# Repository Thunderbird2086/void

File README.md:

# VOID
## An Ergonomic 3x5 Split Keyboard

The VOID keyboard is meticulously designed to offer an ergonomic typing experience with its compact 3x5 layout. It supports a variety of switch types, including CherryMX, Choc V1/V2, and a hybrid configuration.

Similar to the [uniCorne](https://github.com/Thunderbird2086/uniCorne), the VOID keyboard features controller compatibility, hardware handedness, and Nice!View integration. Additionally, for communication between each side in wired keyboards using PR2040/ProMicro, it uses a USB Type-C connector instead of TRRS to avoid short circuit issues that can damage MCUs.

The pinky column is slightly splayed while the others are column staggered. For wireless keyboards, the VOID has a power connector to the MCU and an onboard pogo pin connector to the charger board, which can be directly connected to a battery.

## Images

## Build guide
TODO

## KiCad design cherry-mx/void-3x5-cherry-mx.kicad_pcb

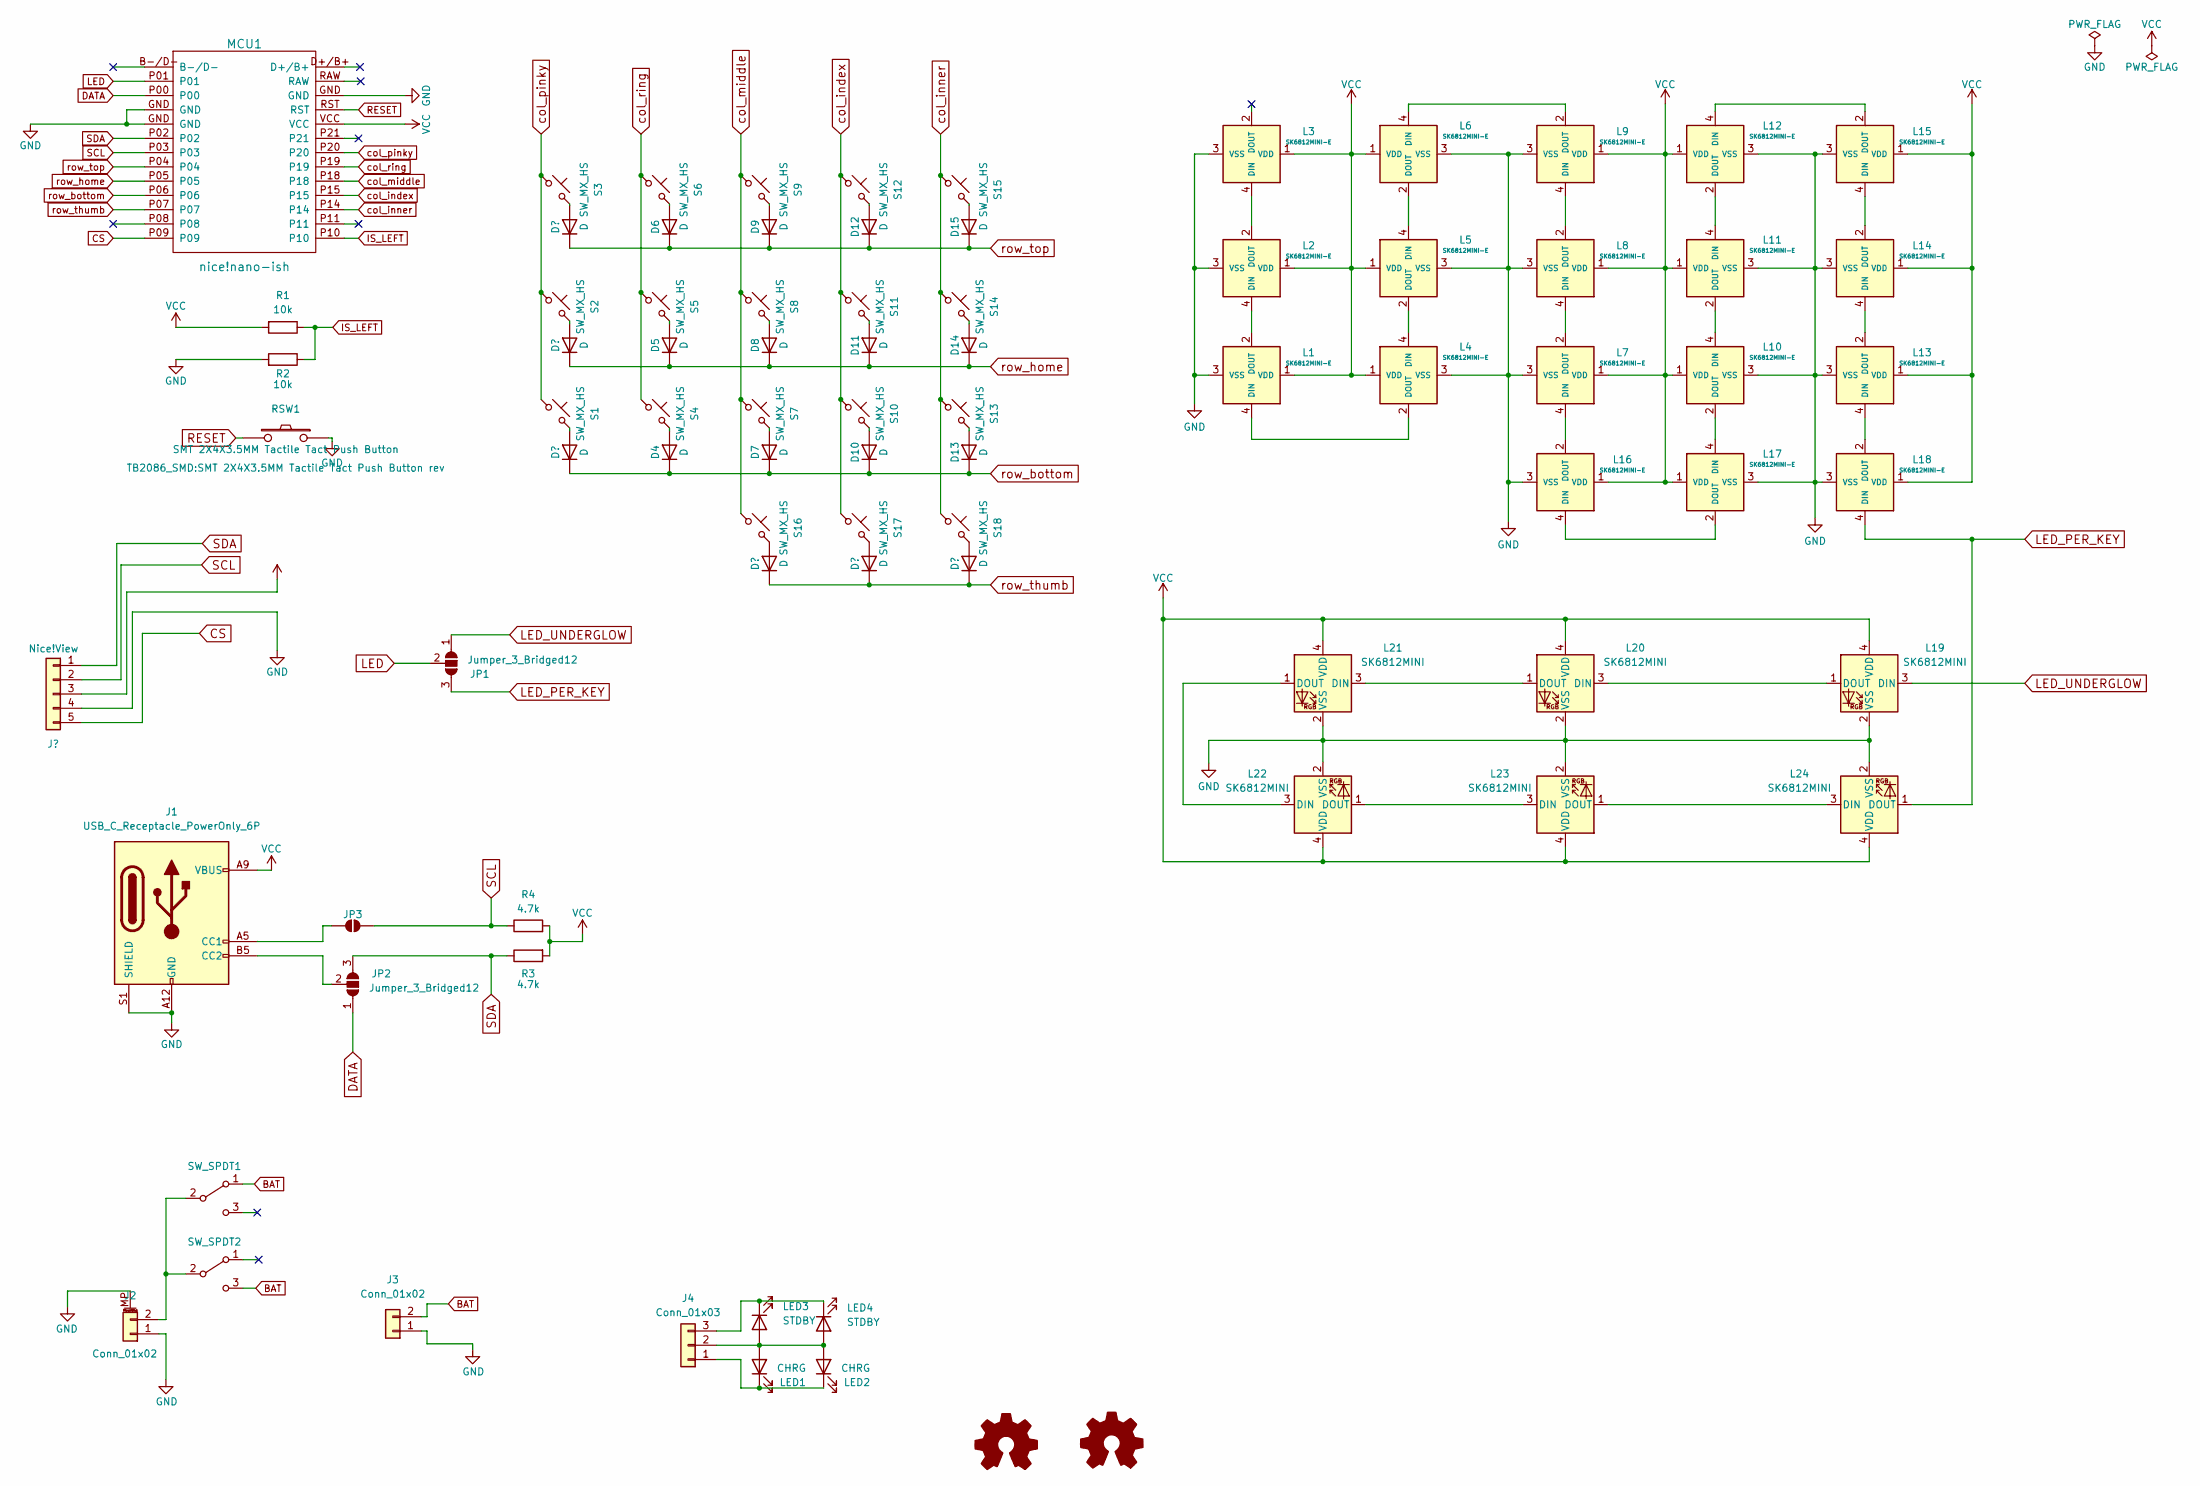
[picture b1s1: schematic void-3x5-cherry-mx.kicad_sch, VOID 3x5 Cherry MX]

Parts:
D1, D2, D3, D4, D5, D6, D7, D8, D9, D10, D11, D12, D13, D14, D15, D16, D17, D18: D; D3_SMD_rev
DISP1: Nice!View; Nice!View_rev
J1: USB_C_Receptacle_PowerOnly_6P; USB-20C-F-6C16_rev
J2: Conn_01x02; JST_PH_S2B-PH-SM4-TB_1x02-1MP_P2.00mm_Horizontal_rev
J3: Conn_01x02; Pogopin_1x02_P2.54mm
J4: Conn_01x03; Pogopin_1x03_P2.54mm
JP1, JP2: Jumper_3_Bridged12; SolderJumper-3_P1.3mm_Open_RoundedPad1.0x1.5mm_rev
JP3: SolderJumper-2_P1.3mm_Open_TrianglePad1.0x1.2mm_rev
L1, L2, L3, L4, L5, L6, L7, L8, L9, L10, L11, L12, L13, L14, L15, L16, L17, L18: SK6812MINI-E; LED_SK6812MINI-E_rev
L19, L20, L21, L22, L23, L24: SK6812MINI; LED_SK6812MINI_PLCC4_3.5x3.5mm_P1.75mm_rev_all
LED1, LED2: CHRG; LED_0603_1608Metric_Pad1.05x0.95mm_HandSolder
LED3, LED4: STDBY; LED_0603_1608Metric_Pad1.05x0.95mm_HandSolder
LOGO1: Logo_Open_ErgoGen; utility_ergogen_logo_rev
LOGO2: Logo_Open_Hardware_Small; OSHW-Logo_5.7x6mm_SilkScreen_rev
MCU1: nice!nano-ish; ProMicro-dn-rev-unrouted
R1, R2: 10k; R_0805_2012Metric_Pad1.20x1.40mm_HandSolder
R3, R4: 4.7k; R_0805_2012Metric_Pad1.20x1.40mm_HandSolder_rev
RSW1: SMT 2X4X3.5MM Tactile Tact Push Button; SMT 2X4X3.5MM Tactile Tact Push Button rev
S1, S2, S3, S4, S5, S6, S7, S8, S9, S10, S11, S12, S13, S14, S15, S16, S17: SW_MX_HS; SW_MX_HS_1u_reversible
S18: SW_MX_HS; SW_MX_HS_1.5u_reversible
SW_SPDT1: SW_SPDT1; SW_SPDT_PCM12
SW_SPDT2: SW_SPDT2; SW_SPDT_PCM12

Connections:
BAT: J3.2, SW_SPDT1.1 (A), SW_SPDT2.3 (C)
CS: DISP1.5, MCU1.P09
DATA: JP2.1 (A), MCU1.P00
GND: DISP1.4, J1.A12 (GND), J1.B12 (GND), J1.S1 (SHIELD), J2.1, J2.MP (MountPin), J3.1, L1.3 (VSS), L2.3 (VSS), L3.3 (VSS), L4.3 (VSS), L5.3 (VSS), L6.3 (VSS), L7.3 (VSS), L8.3 (VSS), L9.3 (VSS), L10.3 (VSS), L11.3 (VSS), L12.3 (VSS), L13.3 (VSS), L14.3 (VSS), L15.3 (VSS), L16.3 (VSS), L17.3 (VSS), L18.3 (VSS), L19.2 (VSS), L20.2 (VSS), L21.2 (VSS), L22.2 (VSS), L23.2 (VSS), L24.2 (VSS), MCU1.GND, R2.2, RSW1.1, RSW1.MP
IS_LEFT: MCU1.P10, R1.1, R2.1
LED: JP1.2 (C), MCU1.P01
LED_PER_KEY: JP1.3 (B), L18.4 (DIN), L24.1 (DOUT)
LED_UNDERGLOW: JP1.1 (A), L19.3 (DIN)
unnamed: D1.2 (A), S1.1
unnamed: D2.2 (A), S2.1
unnamed: D3.2 (A), S3.1
unnamed: D4.2 (A), S4.1
unnamed: D5.2 (A), S5.1
unnamed: D6.2 (A), S6.1
unnamed: D7.2 (A), S7.1
unnamed: D8.2 (A), S8.1
unnamed: D9.2 (A), S9.1
unnamed: D10.2 (A), S10.1
unnamed: D11.2 (A), S11.1
unnamed: D12.2 (A), S12.1
unnamed: D13.2 (A), S13.1
unnamed: D14.2 (A), S14.1
unnamed: D15.2 (A), S15.1
unnamed: D16.2 (A), S16.1
unnamed: D17.2 (A), S17.1
unnamed: D18.2 (A), S18.1
unnamed: J1.A5 (CC1), JP3.2 (B)
unnamed: J1.B5 (CC2), JP2.2 (C)
unnamed: J2.2, SW_SPDT1.2 (B), SW_SPDT2.2 (B)
unnamed: J4.1, LED1.1 (K), LED2.1 (K)
unnamed: J4.2, LED1.2 (A), LED2.2 (A), LED3.2 (A), LED4.2 (A)
unnamed: J4.3, LED3.1 (K), LED4.1 (K)
unnamed: L1.4 (DIN), L4.2 (DOUT)
unnamed: L1.2 (DOUT), L2.4 (DIN)
unnamed: L2.2 (DOUT), L3.4 (DIN)
unnamed: L4.4 (DIN), L5.2 (DOUT)
unnamed: L5.4 (DIN), L6.2 (DOUT)
unnamed: L6.4 (DIN), L9.2 (DOUT)
unnamed: L7.2 (DOUT), L8.4 (DIN)
unnamed: L8.2 (DOUT), L9.4 (DIN)
unnamed: L10.4 (DIN), L11.2 (DOUT)
unnamed: L10.2 (DOUT), L17.4 (DIN)
unnamed: L11.4 (DIN), L12.2 (DOUT)
unnamed: L12.4 (DIN), L15.2 (DOUT)
unnamed: L13.4 (DIN), L18.2 (DOUT)
unnamed: L13.2 (DOUT), L14.4 (DIN)
unnamed: L14.2 (DOUT), L15.4 (DIN)
unnamed: L16.4 (DIN), L17.2 (DOUT)
unnamed: L7.4 (DIN), L16.2 (DOUT)
unnamed: L19.1 (DOUT), L20.3 (DIN)
unnamed: L20.1 (DOUT), L21.3 (DIN)
unnamed: L21.1 (DOUT), L22.3 (DIN)
unnamed: L22.1 (DOUT), L23.3 (DIN)
unnamed: L23.1 (DOUT), L24.3 (DIN)
RESET: MCU1.RST, RSW1.2
SCL: DISP1.2, JP3.1 (A), MCU1.P03, R4.1
SDA: DISP1.1, JP2.3 (B), MCU1.P02, R3.1
VCC: DISP1.3, J1.A9 (VBUS), J1.B9 (VBUS), L1.1 (VDD), L2.1 (VDD), L3.1 (VDD), L4.1 (VDD), L5.1 (VDD), L6.1 (VDD), L7.1 (VDD), L8.1 (VDD), L9.1 (VDD), L10.1 (VDD), L11.1 (VDD), L12.1 (VDD), L13.1 (VDD), L14.1 (VDD), L15.1 (VDD), L16.1 (VDD), L17.1 (VDD), L18.1 (VDD), L19.4 (VDD), L20.4 (VDD), L21.4 (VDD), L22.4 (VDD), L23.4 (VDD), L24.4 (VDD), MCU1.VCC, R1.2, R3.2, R4.2
col_index: MCU1.P15, S10.2, S11.2, S12.2, S17.2
col_inner: MCU1.P14, S13.2, S14.2, S15.2, S18.2
col_middle: MCU1.P18, S7.2, S8.2, S9.2, S16.2
col_pinky: MCU1.P20, S1.2, S2.2, S3.2
col_ring: MCU1.P19, S4.2, S5.2, S6.2
row_bottom: D1.1 (K), D4.1 (K), D7.1 (K), D10.1 (K), D13.1 (K), MCU1.P06
row_home: D2.1 (K), D5.1 (K), D8.1 (K), D11.1 (K), D14.1 (K), MCU1.P05
row_thumb: D16.1 (K), D17.1 (K), D18.1 (K), MCU1.P07
row_top: D3.1 (K), D6.1 (K), D9.1 (K), D12.1 (K), D15.1 (K), MCU1.P04

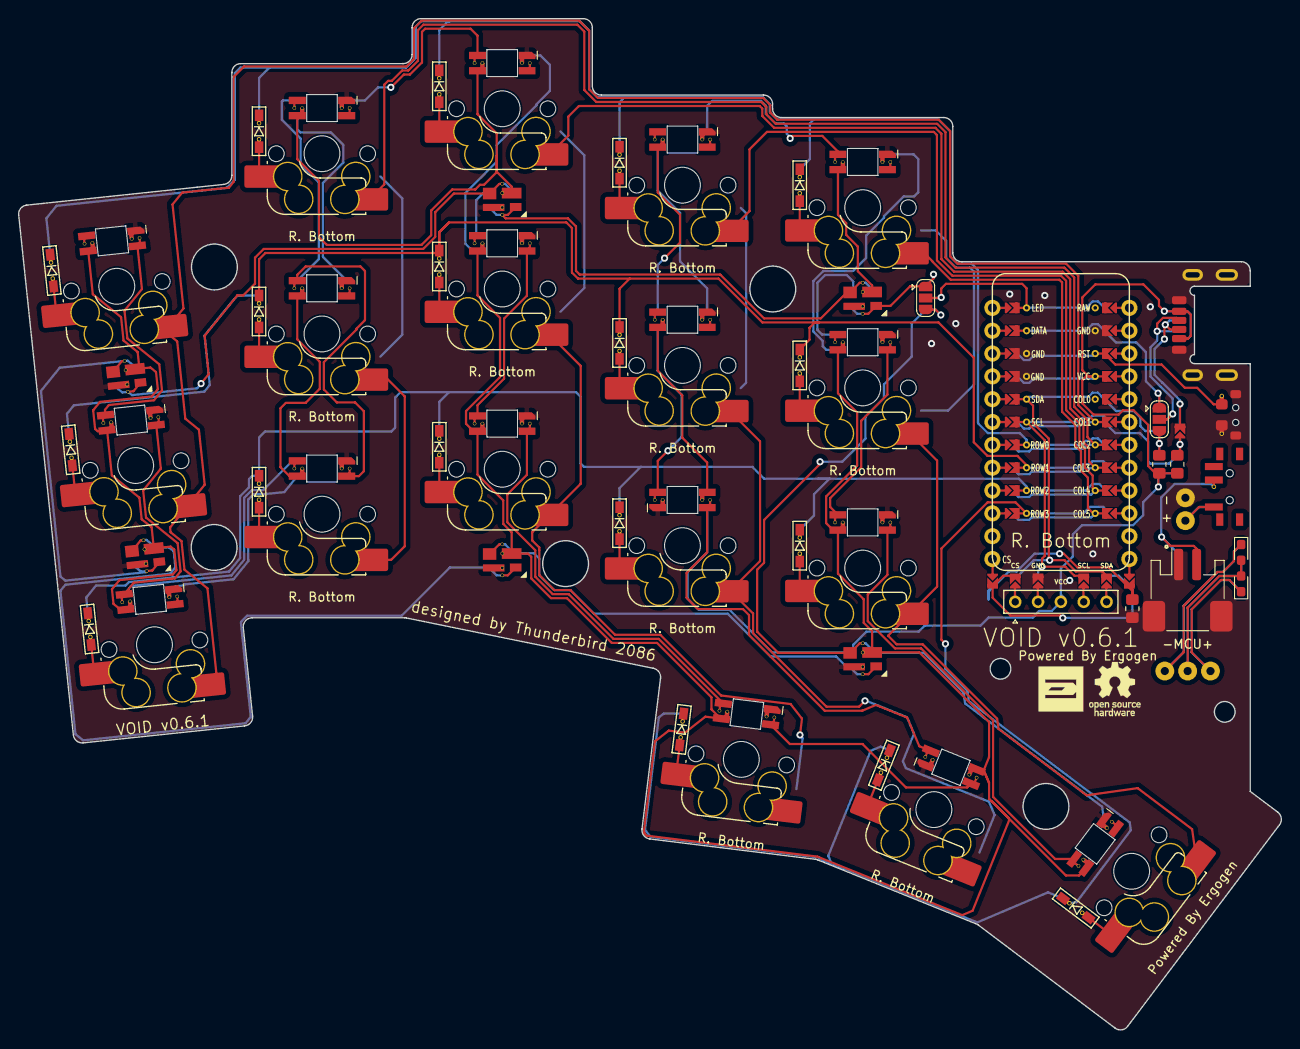
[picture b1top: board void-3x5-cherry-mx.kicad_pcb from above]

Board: 2 copper layers, 140.5 x 112.5 mm, 82 parts (1 on the bottom side), 67 nets.

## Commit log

2024-11-10 bottom plate
2024-11-10 rename
2024-11-10 added hybrid
2024-11-11 added choc
2024-11-13 choc
2024-11-13 github workflow for PCB
2024-11-13 0.5.8 (#1)
    * initial commit
    * bottom plate
    * rename
    * added hybrid
    * added choc
    * choc
2024-11-13 quick fix
2024-11-13 quick fix (#2)
2024-11-13 added kibot.yaml
2024-11-13 added kibot.yaml (#3)
2024-11-17 updated mcu footprint for choc
2024-11-17 added holes for oled window
2024-11-17 hybrid top plate
2024-11-17 added hybrid top plate
2024-11-17 Choc (#4)
    * updated mcu footprint for choc
    * added holes for oled window
    * hybrid top plate
    * added hybrid top plate
2024-11-17 workflow for plates
2024-11-17 workflow for plates (#5)
2024-11-17 fix workflow for plates
2024-11-17 minor fix
2024-11-17 Fix workflow (#6)
    * fix workflow for plates
    * minor fix
2024-11-18 more plates
2024-11-18 updated workflow
2024-11-18 mcu cover
2024-11-18 small change
2024-11-18 Mcu cover (#7)
    * more plates
    * updated workflow
    * mcu cover
    * small change
2024-11-18 amended hybrid top
2024-11-18 amended hybrid top (#8)
2024-11-20 fixed mcu window size
2024-11-20 fixed mcu window size (#9)
2024-11-24 added step/stl for cases
2024-11-24 added step/stl for cases (#10)
2024-11-24 added missing step files
2024-11-24 added missing step files (#11)
2024-11-26 fixed bridge for hybrid-mx
2024-11-26 fixed bridge for hybrid-mx (#13)
2025-01-30 usb-c mod for hybrid
    * updated
    - submodule
    - ergogen yaml
    - schematic and pcb
2025-01-30 updated cherry-mx
    usb-c for communication between left and right hand sides
2025-01-30 updated choc
2025-01-30 updated choc
    * fixed corner
2025-01-31 void-choc
    * ergogen
    - bottom plate
    - charger plate
2025-01-31 updated ergogen
    * cherry-mx
    * hybrid-mx
2025-02-01 updated ergogen for VOID Choc
2025-02-01 refreshed submodule
2025-02-01 updated ergogen yaml
2025-02-01 updated PCBs
2025-02-01 updated version
2025-02-01 Changed TRRS to USB-C connector (#14)
    * usb-c mod for hybrid
    * updated
    - submodule
    - ergogen yaml
    - schematic and pcb
    * updated cherry-mx
2025-02-02 updated submodule
2025-02-02 small touches
2025-02-02 changed version
2025-02-02 Small tweaks (#15)
    * updated submodule
    * small touches
    * changed version
2025-02-02 fix version
2025-02-02 updated PCB
2025-02-02 Quick fixes (#16)
    * fix version
    * updated PCB
2025-02-02 updated ergogen files
2025-02-02 updated kicad data
2025-02-02 Fix ergogen (#17)
    * refreshed submodule
    * updated ergogen files
    * updated kicad data
2025-02-05 fixed broken link to uniCorne
2025-02-05 Readme (#18)
    * updated readme
    * fixed broken link to uniCorne
